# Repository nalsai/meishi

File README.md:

# meishi

My business card, as well as a QMK powered macro keyboard.

<https://en.nalsai.de/meishi/> (page coming soon™)

## KiCad libraries used

- <https://github.com/daprice/keyswitches.pretty> (switch footprint)
- <https://github.com/keebio/Keebio-Parts.pretty> (Pro Micro footprint)

&nbsp;

## Thanks for the inspiration

- <https://medium.com/henngeblog/mechanical-keyboard-business-card-83385aa8bc29> (https://github.com/lukas-reineke/meishi)
- <https://github.com/Biacco42/meishi>
- <https://www.youtube.com/watch?v=rEdWV4Augfc>

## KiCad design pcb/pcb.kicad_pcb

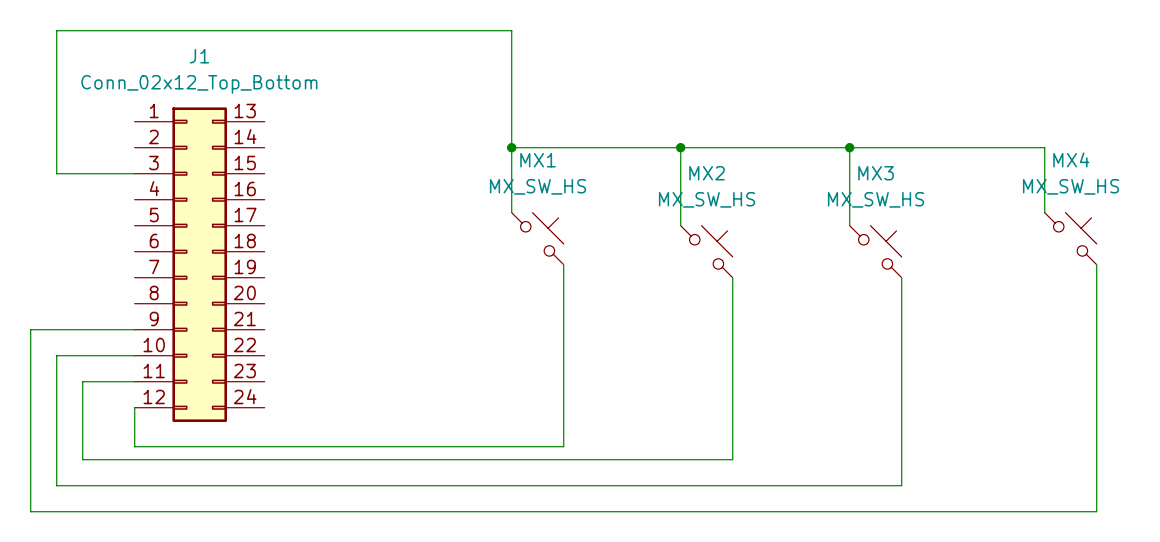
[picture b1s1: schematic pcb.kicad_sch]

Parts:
J1: Conn_02x12_Top_Bottom; ArduinoProMicro
MX1, MX2, MX3, MX4: MX_SW_HS; Kailh_socket_MX_optional

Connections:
unnamed: J1.3, MX1.1, MX2.1, MX3.1, MX4.1
unnamed: J1.9, MX4.2
unnamed: J1.10, MX3.2
unnamed: J1.11, MX2.2
unnamed: J1.12, MX1.2

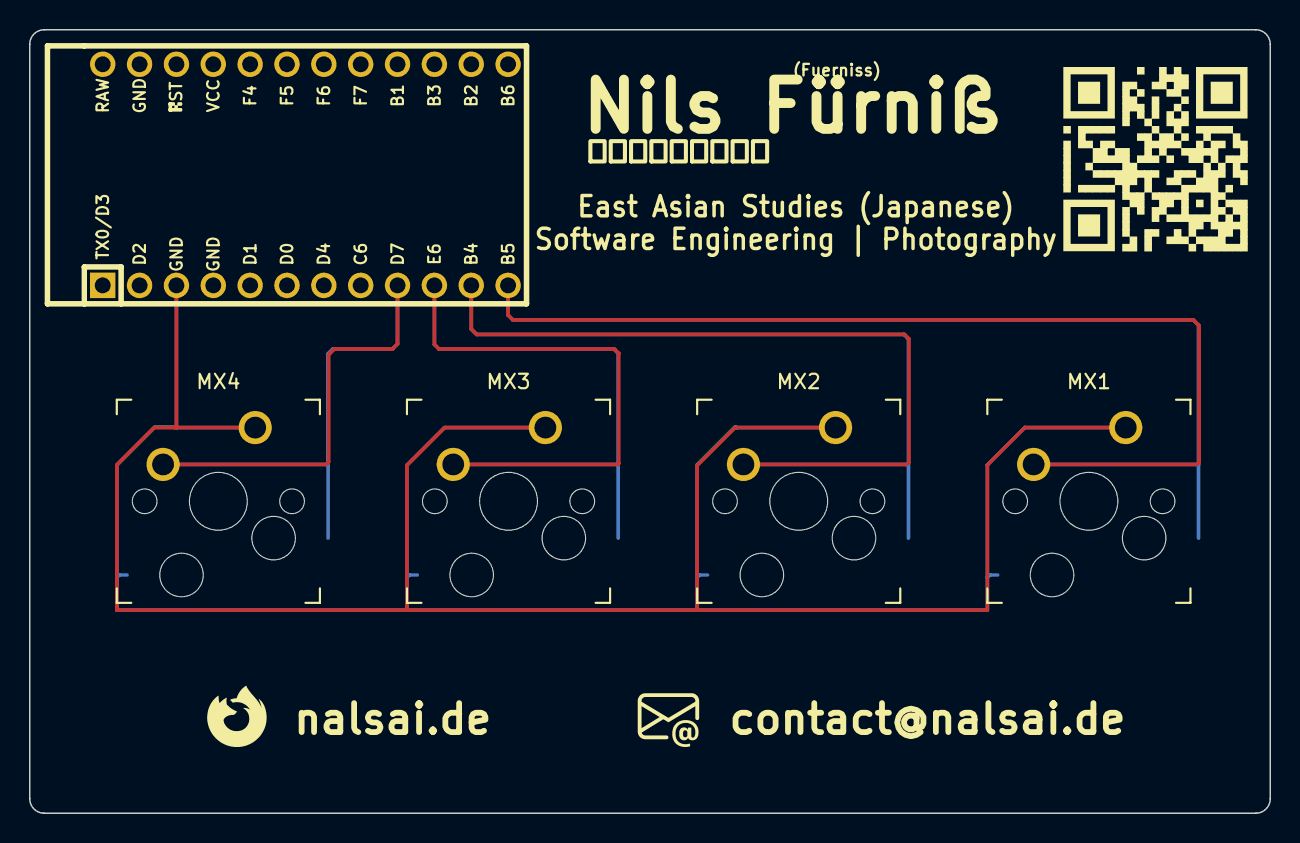
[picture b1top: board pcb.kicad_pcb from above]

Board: 2 copper layers, 85.5 x 54.0 mm, 5 parts (0 on the bottom side), 5 nets.

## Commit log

2023-08-13 Add gerber files
